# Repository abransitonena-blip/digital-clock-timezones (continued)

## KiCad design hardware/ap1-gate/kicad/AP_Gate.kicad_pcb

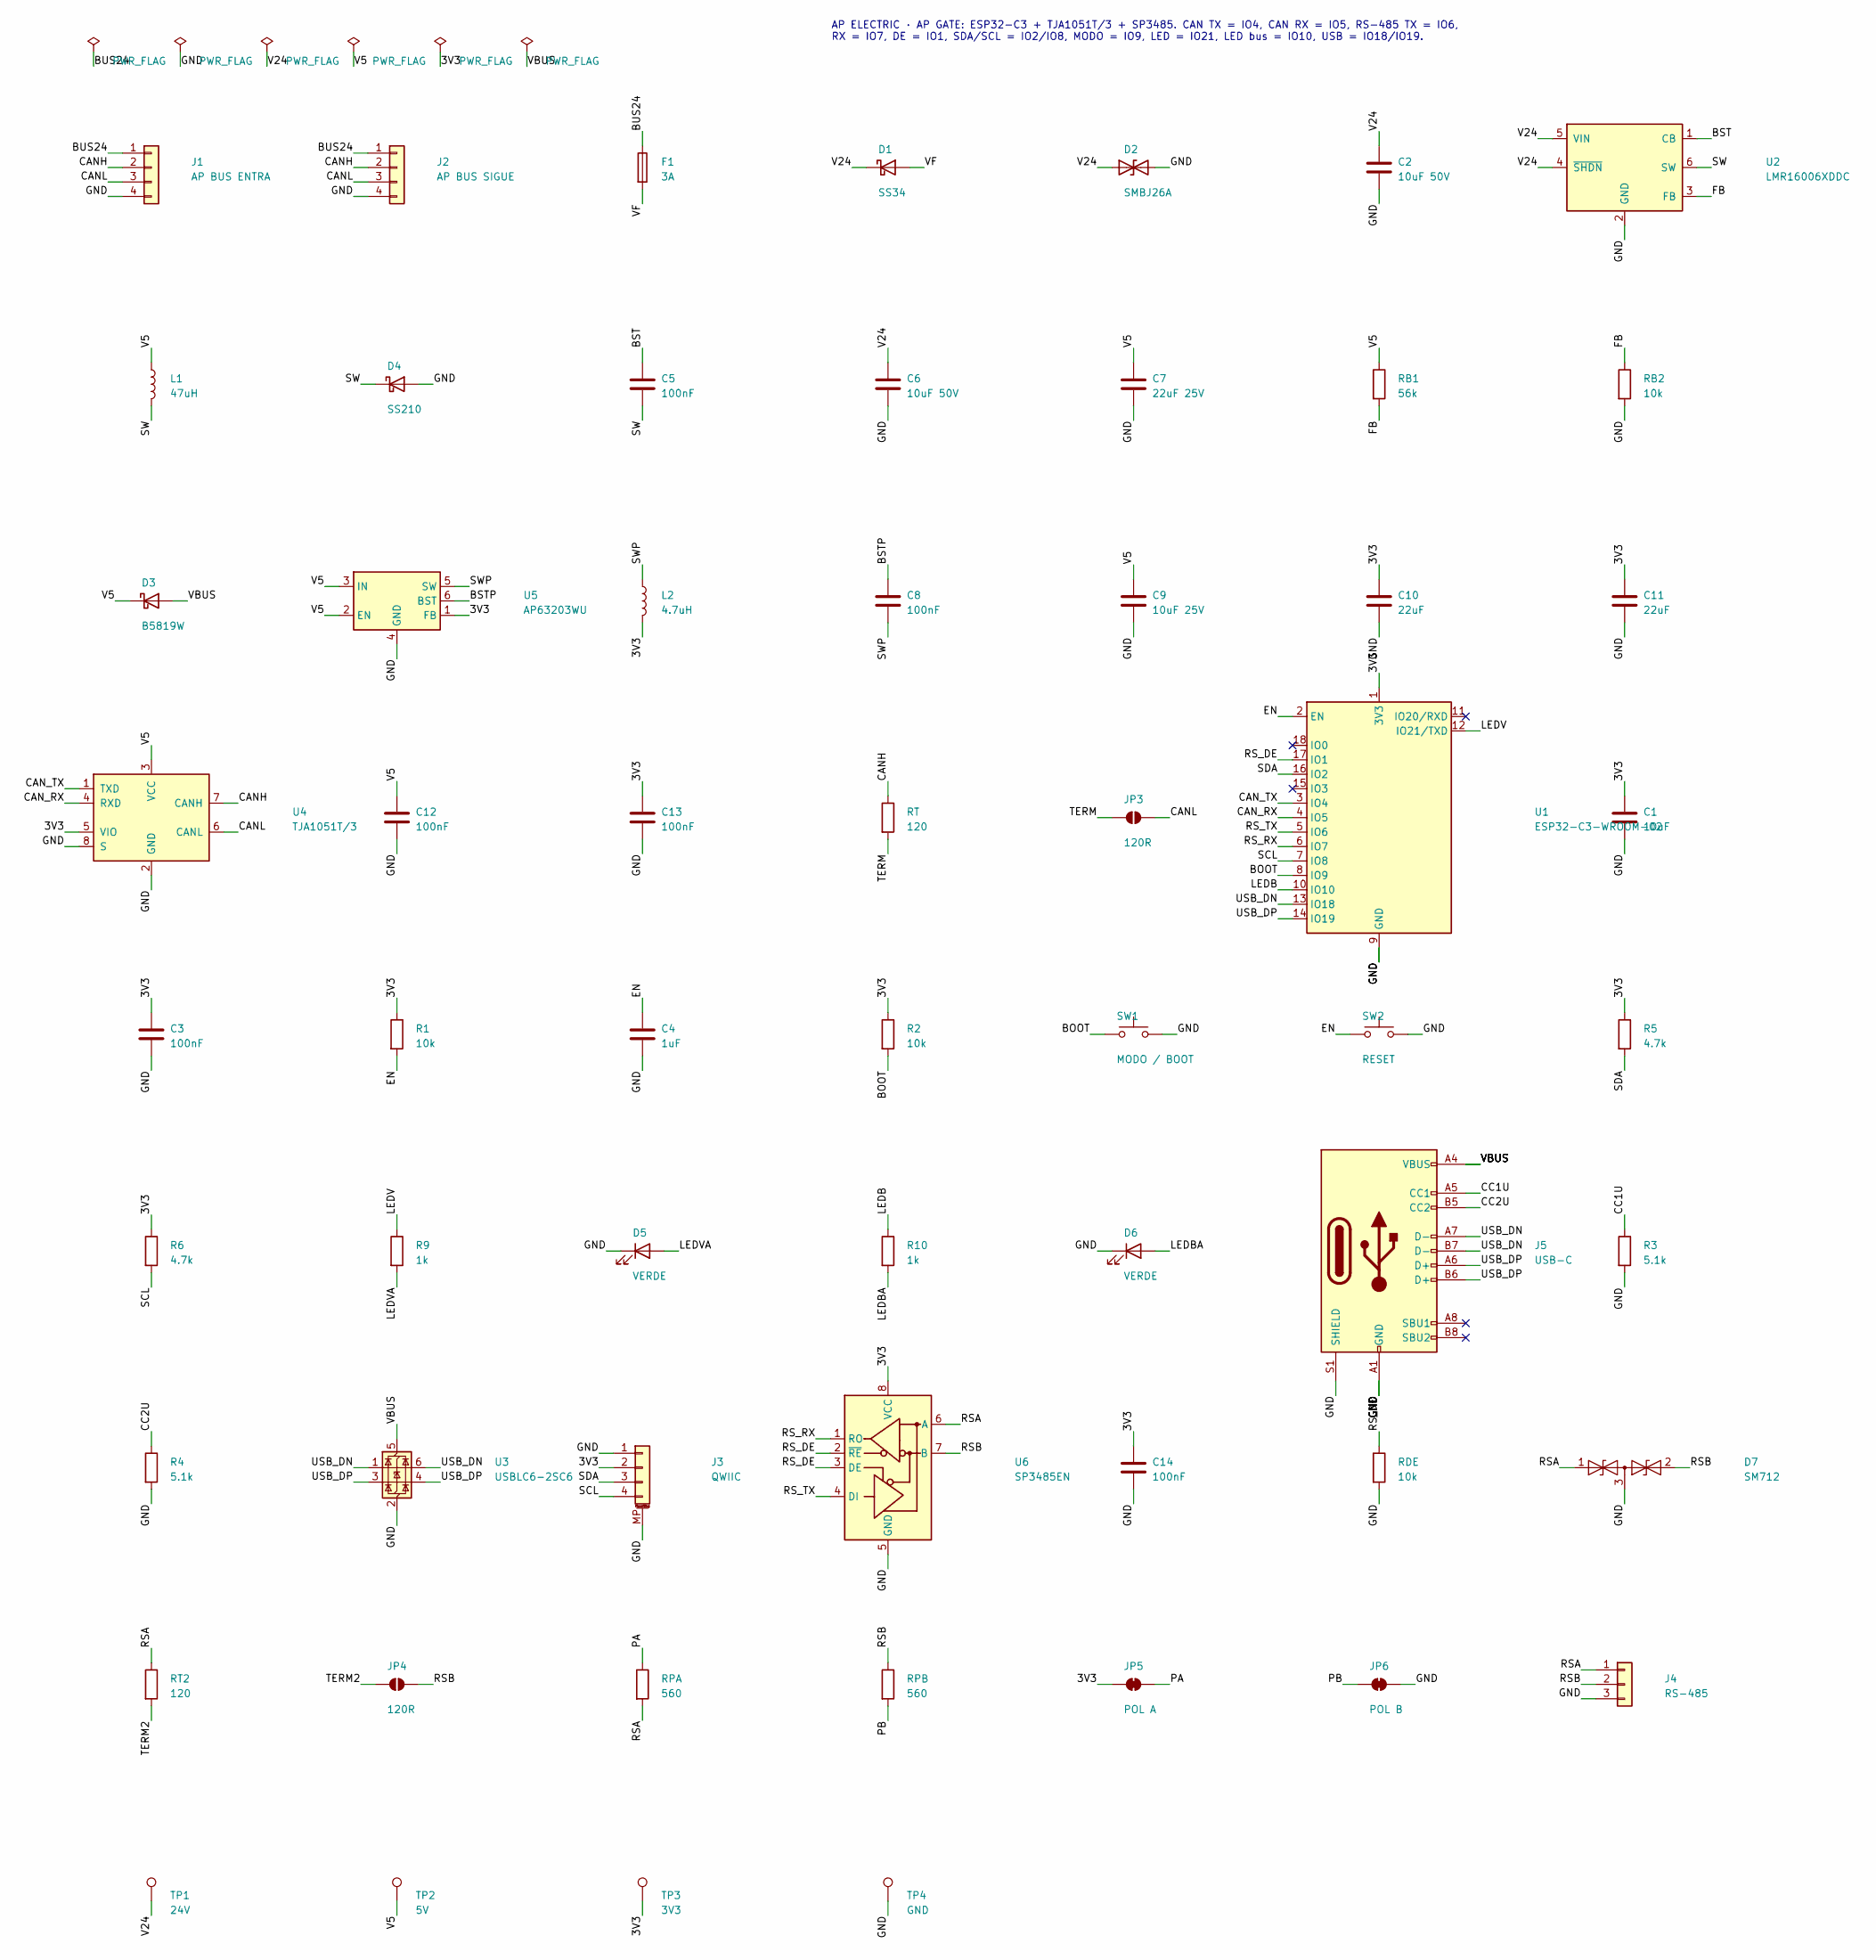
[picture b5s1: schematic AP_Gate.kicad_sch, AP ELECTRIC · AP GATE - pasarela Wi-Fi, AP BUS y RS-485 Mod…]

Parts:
C1: 10uF; C_0805_2012Metric
C2, C6: 10uF 50V; C_1206_3216Metric
C3, C5, C8, C12, C13, C14: 100nF; C_0603_1608Metric
C4: 1uF; C_0603_1608Metric
C7: 22uF 25V; C_1206_3216Metric
C9: 10uF 25V; C_1206_3216Metric
C10, C11: 22uF; C_0805_2012Metric
D1: SS34; D_SMA
D2: SMBJ26A; D_SMB
D3: B5819W; D_SOD-123
D4: SS210; D_SMA
D5, D6: VERDE; LED_0603_1608Metric
D7: SM712; SOT-23
F1: 3A; Fuse_1206_3216Metric
J1: AP BUS ENTRA; JST_XH_B4B-XH-A_1x04_P2.50mm_Vertical
J2: AP BUS SIGUE; JST_XH_B4B-XH-A_1x04_P2.50mm_Vertical
J3: QWIIC; JST_SH_SM04B-SRSS-TB_1x04-1MP_P1.00mm_Horizontal
J4: RS-485; JST_XH_B3B-XH-A_1x03_P2.50mm_Vertical
J5: USB-C; USB_C_Receptacle_HRO_TYPE-C-31-M-12
JP3, JP4: 120R; SolderJumper-2_P1.3mm_Open_RoundedPad1.0x1.5mm
JP5: POL A; SolderJumper-2_P1.3mm_Bridged_RoundedPad1.0x1.5mm
JP6: POL B; SolderJumper-2_P1.3mm_Bridged_RoundedPad1.0x1.5mm
L1: 47uH; L_Changjiang_FNR4030S
L2: 4.7uH; L_Changjiang_FNR4030S
R1, R2: 10k; R_0603_1608Metric
R3, R4: 5.1k; R_0603_1608Metric
R5, R6: 4.7k; R_0603_1608Metric
R9, R10: 1k; R_0603_1608Metric
RB1: 56k; R_0603_1608Metric
RB2: 10k; R_0603_1608Metric
RDE: 10k; R_0603_1608Metric
RPA: 560; R_0603_1608Metric
RPB: 560; R_0603_1608Metric
RT, RT2: 120; R_1206_3216Metric
SW1: MODO / BOOT; SW_Push_1P1T_XKB_TS-1187A
SW2: RESET; SW_Push_1P1T_XKB_TS-1187A
TP1: 24V; TestPoint_Pad_D1.5mm
TP2: 5V; TestPoint_Pad_D1.5mm
TP3: 3V3; TestPoint_Pad_D1.5mm
TP4: GND; TestPoint_Pad_D1.5mm
U1: ESP32-C3-WROOM-02; ESP32-C3-WROOM-02_JLC
U2: LMR16006XDDC; SOT-23-6
U3: USBLC6-2SC6; SOT-23-6
U4: TJA1051T/3; SOIC-8_3.9x4.9mm_P1.27mm
U5: AP63203WU; TSOT-23-6
U6: SP3485EN; SOIC-8_3.9x4.9mm_P1.27mm

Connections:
/3V3: C1.1, C3.1, C10.1, C11.1, C13.1, C14.1, J3.2, JP5.1 (A), L2.2, R1.1, R2.1, R5.1, R6.1, TP3.1, U1.1 (3V3), U4.5 (VIO), U5.1 (FB), U6.8 (VCC)
/BOOT: R2.2, SW1.1, U1.8 (IO9)
/BST: C5.1, U2.1 (CB)
/BSTP: C8.1, U5.6 (BST)
/BUS24: F1.1, J1.1, J2.1
/CANH: J1.2, J2.2, RT.1, U4.7 (CANH)
/CANL: J1.3, J2.3, JP3.2 (B), U4.6 (CANL)
/CAN_RX: U1.4 (IO5), U4.4 (RXD)
/CAN_TX: U1.3 (IO4), U4.1 (TXD)
/CC1U: J5.A5 (CC1), R3.1
/CC2U: J5.B5 (CC2), R4.1
/EN: C4.1, R1.2, SW2.1, U1.2 (EN)
/FB: RB1.2, RB2.1, U2.3 (FB)
/GND: C1.2, C2.2, C3.2, C4.2, C6.2, C7.2, C9.2, C10.2, C11.2, C12.2, C13.2, C14.2, D2.2 (A2), D4.2 (A), D5.1 (K), D6.1 (K), D7.3 (common), J1.4, J2.4, J3.1, J3.MP (MountPin), J4.3, J5.A1 (GND), J5.A12 (GND), J5.B1 (GND), J5.B12 (GND), J5.S1 (SHIELD), JP6.2 (B), R3.2, R4.2, RB2.2, RDE.2, SW1.2, SW2.2, TP4.1, U1.9 (GND), U1.19 (GND), U2.2 (GND), U3.2 (GND), U4.2 (GND), U4.8 (S), U5.4 (GND), U6.5 (GND)
/LEDB: R10.1, U1.10 (IO10)
/LEDBA: D6.2 (A), R10.2
/LEDV: R9.1, U1.12 (IO21/TXD)
/LEDVA: D5.2 (A), R9.2
/PA: JP5.2 (B), RPA.1
/PB: JP6.1 (A), RPB.2
/RSA: D7.1 (A1), J4.1, RPA.2, RT2.1, U6.6 (A)
/RSB: D7.2 (A2), J4.2, JP4.2 (B), RPB.1, U6.7 (B)
/RS_DE: RDE.1, U1.17 (IO1), U6.2 (~RE), U6.3 (DE)
/RS_RX: U1.6 (IO7), U6.1 (RO)
/RS_TX: U1.5 (IO6), U6.4 (DI)
/SCL: J3.4, R6.2, U1.7 (IO8)
/SDA: J3.3, R5.2, U1.16 (IO2)
/SW: C5.2, D4.1 (K), L1.2, U2.6 (SW)
/SWP: C8.2, L2.1, U5.5 (SW)
/TERM: JP3.1 (A), RT.2
/TERM2: JP4.1 (A), RT2.2
/USB_DN: J5.A7 (D-), J5.B7 (D-), U1.13 (IO18), U3.1 (I/O1), U3.6 (I/O1)
/USB_DP: J5.A6 (D+), J5.B6 (D+), U1.14 (IO19), U3.3 (I/O2), U3.4 (I/O2)
/V5: C7.1, C9.1, C12.1, D3.1 (K), L1.1, RB1.1, TP2.1, U4.3 (VCC), U5.2 (EN), U5.3 (IN)
/V24: C2.1, C6.1, D1.1 (K), D2.1 (A1), TP1.1, U2.4 (~SHDN), U2.5 (VIN)
/VBUS: D3.2 (A), J5.A4 (VBUS), J5.A9 (VBUS), J5.B4 (VBUS), J5.B9 (VBUS), U3.5 (VBUS)
/VF: D1.2 (A), F1.2

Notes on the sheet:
AP ELECTRIC · AP GATE: ESP32-C3 + TJA1051T/3 + SP3485. CAN TX = IO4, CAN RX = IO5, RS-485 TX = IO6, RX = IO7, DE = IO1, SDA/SCL = IO2/IO8, MODO = IO9, LED = IO21, LED bus = IO10, USB = IO18/IO19.

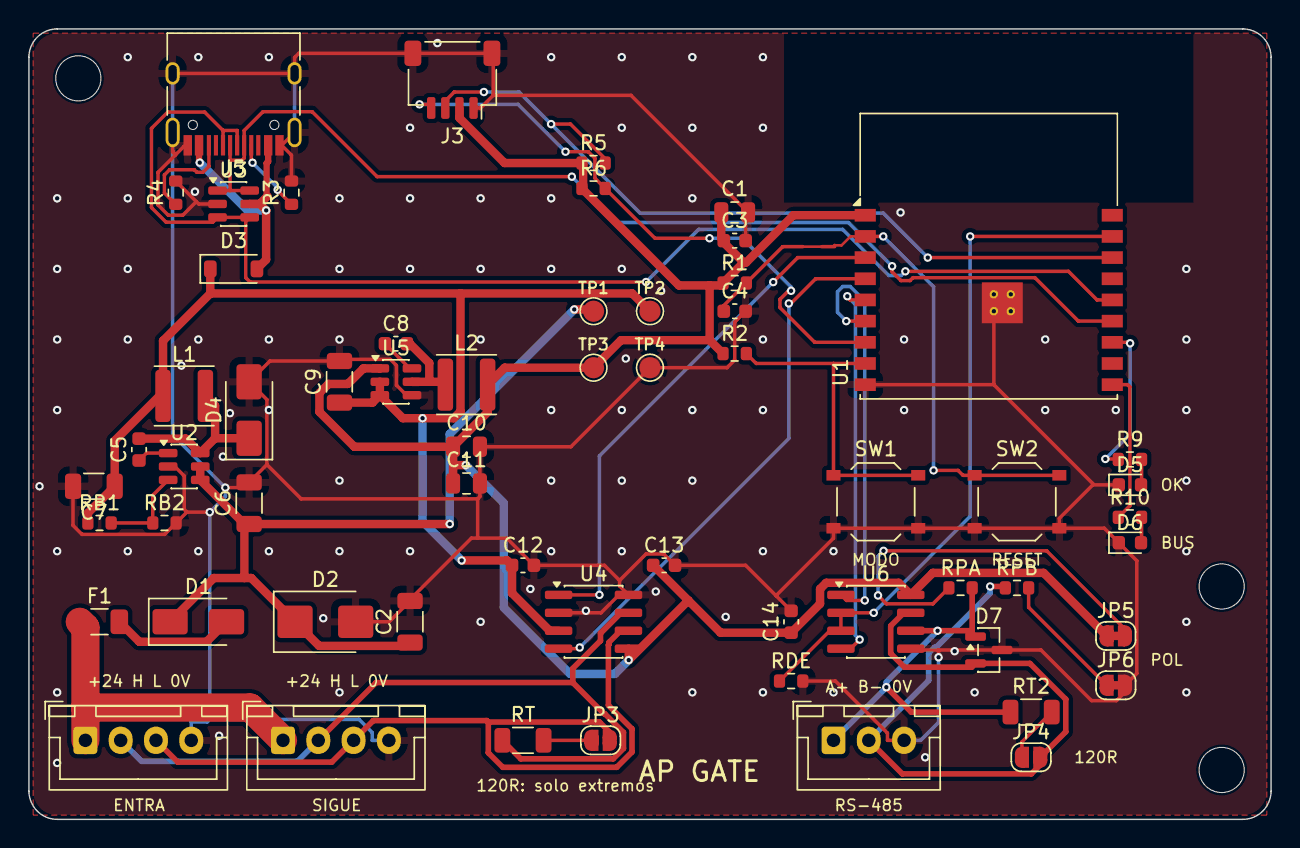
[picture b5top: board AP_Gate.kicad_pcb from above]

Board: 2 copper layers, 88.0 x 56.0 mm, 63 parts (0 on the bottom side), 37 nets.

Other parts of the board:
H1, H2, H3: MountingHole_3.2mm_M3

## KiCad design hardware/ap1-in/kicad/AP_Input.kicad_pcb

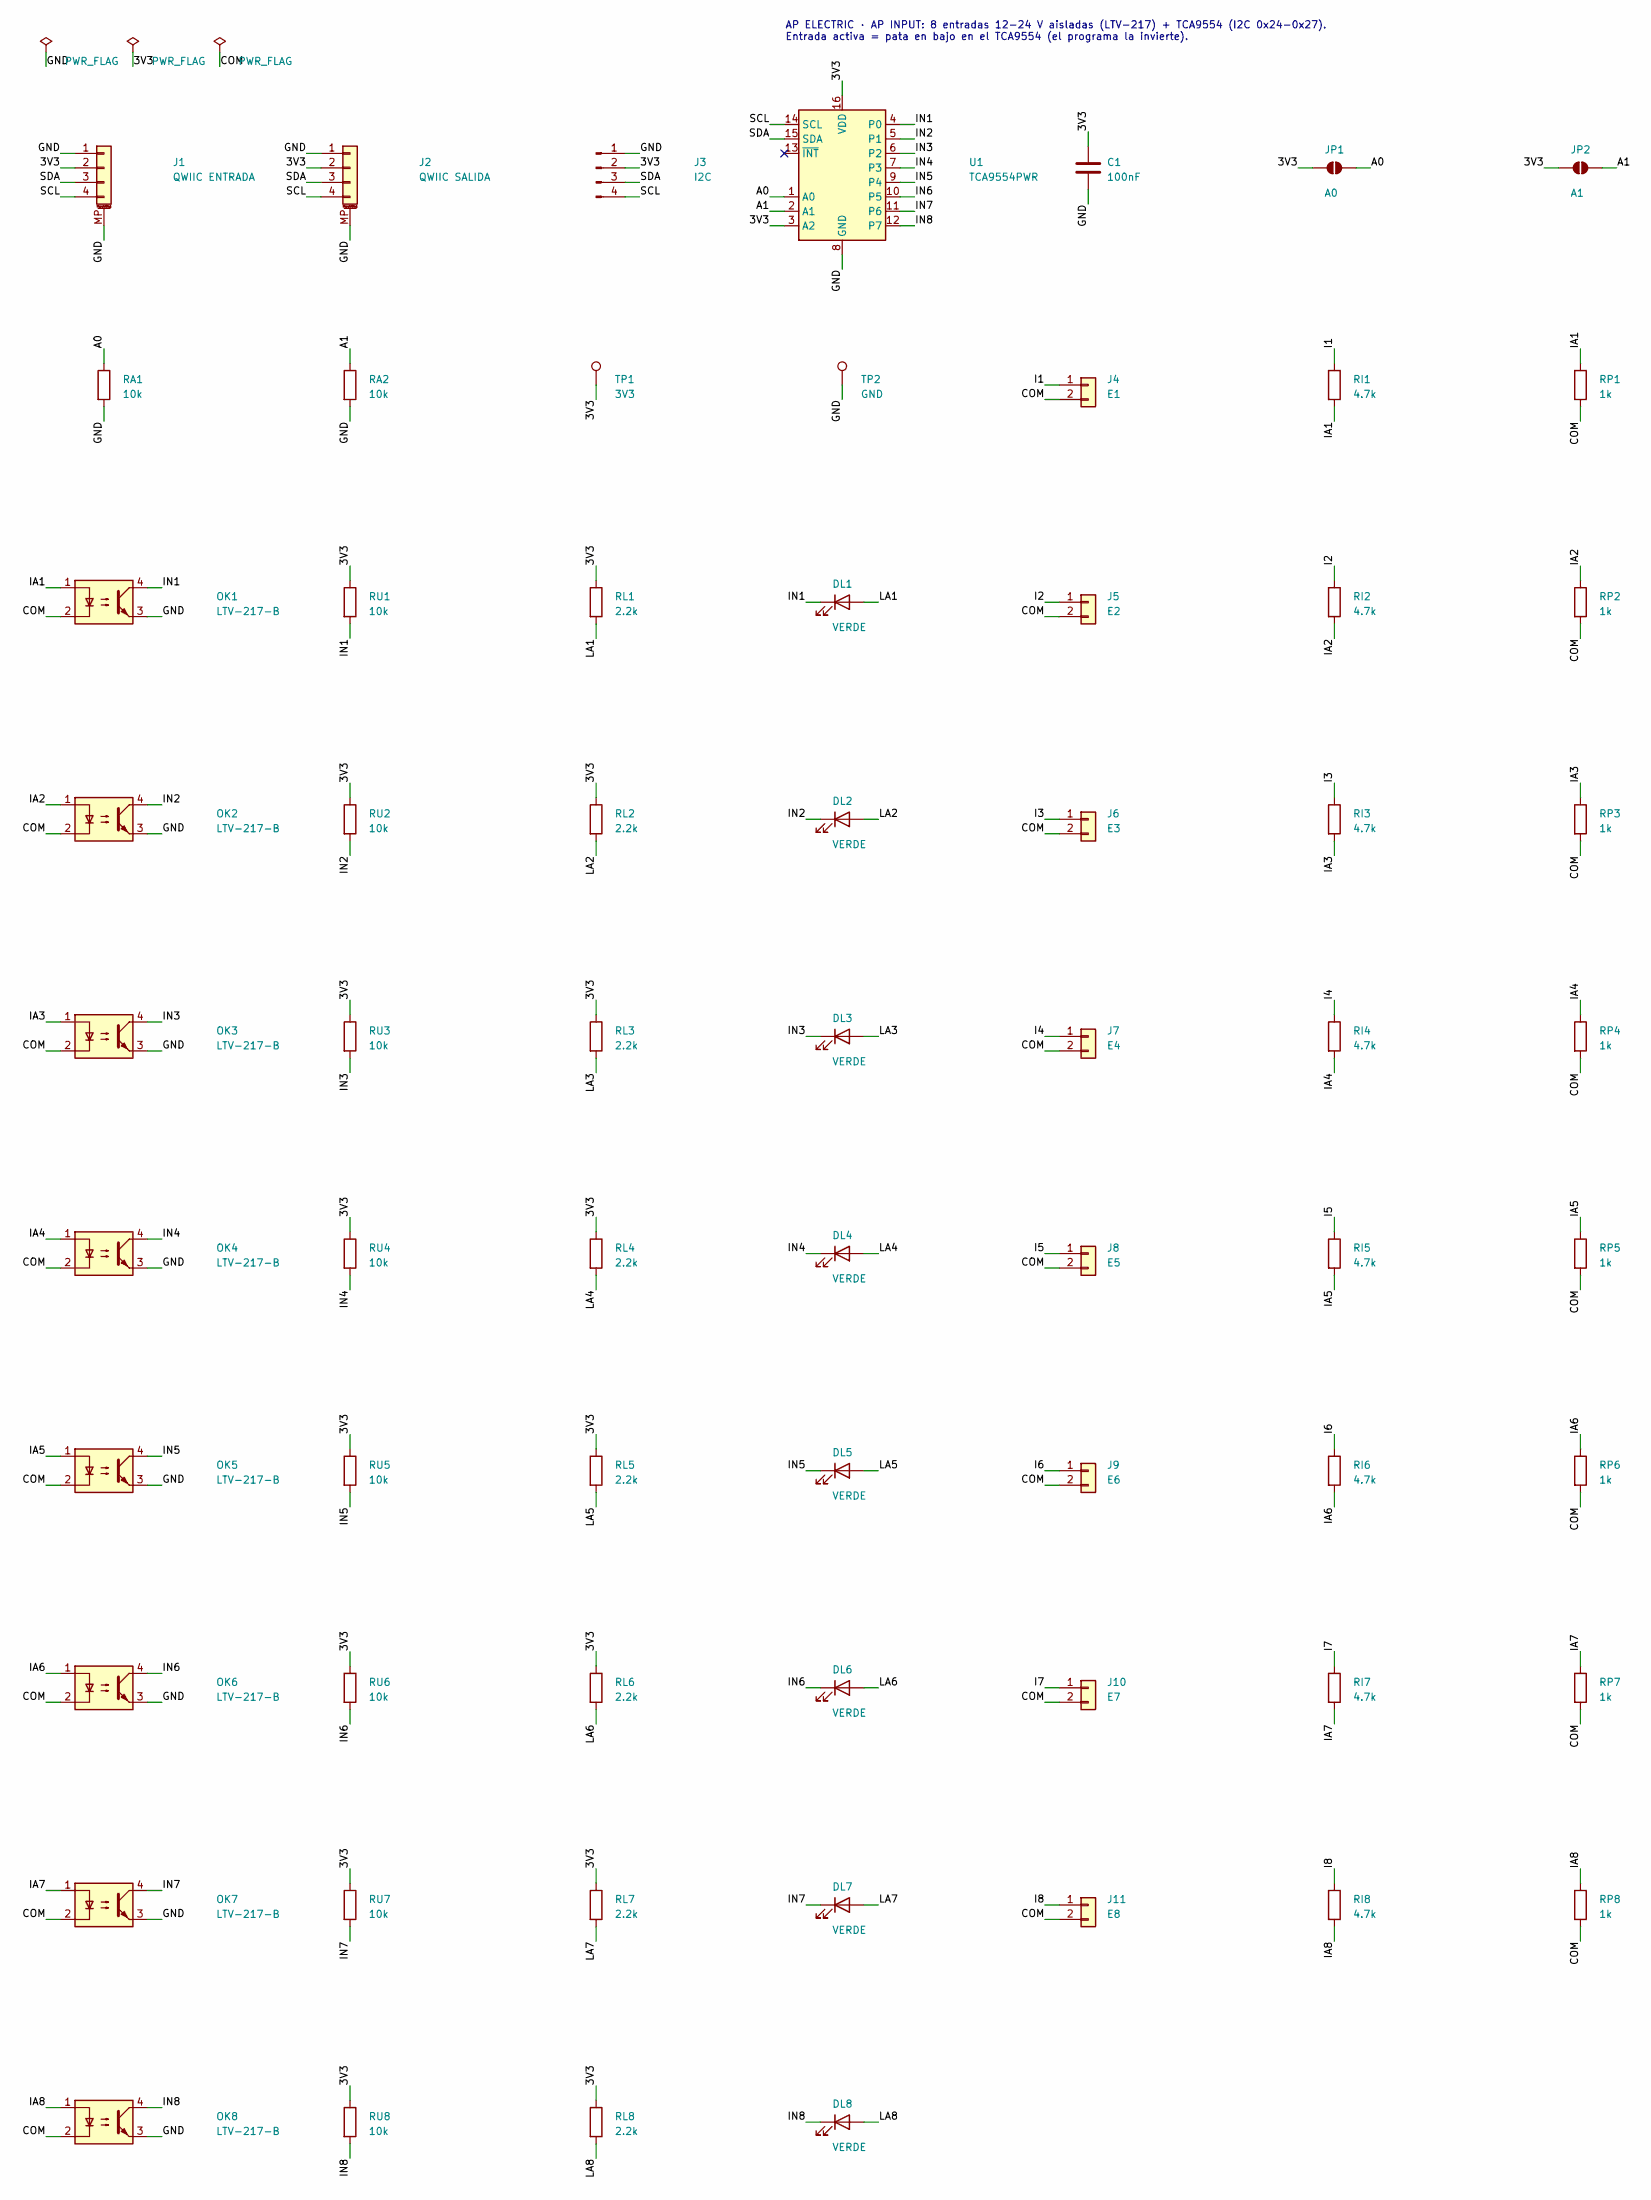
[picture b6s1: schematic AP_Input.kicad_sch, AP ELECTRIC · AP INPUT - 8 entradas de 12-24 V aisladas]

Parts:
C1: 100nF; C_0603_1608Metric
DL1, DL2, DL3, DL4, DL5, DL6, DL7, DL8: VERDE; LED_0603_1608Metric
J1: QWIIC ENTRADA; JST_SH_SM04B-SRSS-TB_1x04-1MP_P1.00mm_Horizontal
J2: QWIIC SALIDA; JST_SH_SM04B-SRSS-TB_1x04-1MP_P1.00mm_Horizontal
J3: I2C; PinHeader_1x04_P2.54mm_Vertical
J4: E1; JST_XH_B2B-XH-A_1x02_P2.50mm_Vertical
J5: E2; JST_XH_B2B-XH-A_1x02_P2.50mm_Vertical
J6: E3; JST_XH_B2B-XH-A_1x02_P2.50mm_Vertical
J7: E4; JST_XH_B2B-XH-A_1x02_P2.50mm_Vertical
J8: E5; JST_XH_B2B-XH-A_1x02_P2.50mm_Vertical
J9: E6; JST_XH_B2B-XH-A_1x02_P2.50mm_Vertical
J10: E7; JST_XH_B2B-XH-A_1x02_P2.50mm_Vertical
J11: E8; JST_XH_B2B-XH-A_1x02_P2.50mm_Vertical
JP1: A0; SolderJumper-2_P1.3mm_Open_RoundedPad1.0x1.5mm
JP2: A1; SolderJumper-2_P1.3mm_Open_RoundedPad1.0x1.5mm
OK1, OK2, OK3, OK4, OK5, OK6, OK7, OK8: LTV-217-B; SOP-4_4.4x2.6mm_P1.27mm
RA1, RA2: 10k; R_0603_1608Metric
RI1, RI2, RI3, RI4, RI5, RI6, RI7, RI8: 4.7k; R_1206_3216Metric
RL1, RL2, RL3, RL4, RL5, RL6, RL7, RL8: 2.2k; R_0603_1608Metric
RP1, RP2, RP3, RP4, RP5, RP6, RP7, RP8: 1k; R_0603_1608Metric
RU1, RU2, RU3, RU4, RU5, RU6, RU7, RU8: 10k; R_0603_1608Metric
TP1: 3V3; TestPoint_Pad_D1.5mm
TP2: GND; TestPoint_Pad_D1.5mm
U1: TCA9554PWR; TSSOP-16_4.4x5mm_P0.65mm

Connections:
/3V3: C1.1, J1.2, J2.2, J3.2, JP1.1 (A), JP2.1 (A), RL1.1, RL2.1, RL3.1, RL4.1, RL5.1, RL6.1, RL7.1, RL8.1, RU1.1, RU2.1, RU3.1, RU4.1, RU5.1, RU6.1, RU7.1, RU8.1, TP1.1, U1.3 (A2), U1.16 (VDD)
/A0: JP1.2 (B), RA1.1, U1.1 (A0)
/A1: JP2.2 (B), RA2.1, U1.2 (A1)
/COM: J4.2, J5.2, J6.2, J7.2, J8.2, J9.2, J10.2, J11.2, OK1.2, OK2.2, OK3.2, OK4.2, OK5.2, OK6.2, OK7.2, OK8.2, RP1.2, RP2.2, RP3.2, RP4.2, RP5.2, RP6.2, RP7.2, RP8.2
/GND: C1.2, J1.1, J1.MP (MountPin), J2.1, J2.MP (MountPin), J3.1, OK1.3, OK2.3, OK3.3, OK4.3, OK5.3, OK6.3, OK7.3, OK8.3, RA1.2, RA2.2, TP2.1, U1.8 (GND)
/I1: J4.1, RI1.1
/I2: J5.1, RI2.1
/I3: J6.1, RI3.1
/I4: J7.1, RI4.1
/I5: J8.1, RI5.1
/I6: J9.1, RI6.1
/I7: J10.1, RI7.1
/I8: J11.1, RI8.1
/IA1: OK1.1, RI1.2, RP1.1
/IA2: OK2.1, RI2.2, RP2.1
/IA3: OK3.1, RI3.2, RP3.1
/IA4: OK4.1, RI4.2, RP4.1
/IA5: OK5.1, RI5.2, RP5.1
/IA6: OK6.1, RI6.2, RP6.1
/IA7: OK7.1, RI7.2, RP7.1
/IA8: OK8.1, RI8.2, RP8.1
/IN1: DL1.1 (K), OK1.4, RU1.2, U1.4 (P0)
/IN2: DL2.1 (K), OK2.4, RU2.2, U1.5 (P1)
/IN3: DL3.1 (K), OK3.4, RU3.2, U1.6 (P2)
/IN4: DL4.1 (K), OK4.4, RU4.2, U1.7 (P3)
/IN5: DL5.1 (K), OK5.4, RU5.2, U1.9 (P4)
/IN6: DL6.1 (K), OK6.4, RU6.2, U1.10 (P5)
/IN7: DL7.1 (K), OK7.4, RU7.2, U1.11 (P6)
/IN8: DL8.1 (K), OK8.4, RU8.2, U1.12 (P7)
/LA1: DL1.2 (A), RL1.2
/LA2: DL2.2 (A), RL2.2
/LA3: DL3.2 (A), RL3.2
/LA4: DL4.2 (A), RL4.2
/LA5: DL5.2 (A), RL5.2
/LA6: DL6.2 (A), RL6.2
/LA7: DL7.2 (A), RL7.2
/LA8: DL8.2 (A), RL8.2
/SCL: J1.4, J2.4, J3.4, U1.14 (SCL)
/SDA: J1.3, J2.3, J3.3, U1.15 (SDA)

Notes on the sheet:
AP ELECTRIC · AP INPUT: 8 entradas 12-24 V aisladas (LTV-217) + TCA9554 (I2C 0x24-0x27). Entrada activa = pata en bajo en el TCA9554 (el programa la invierte).

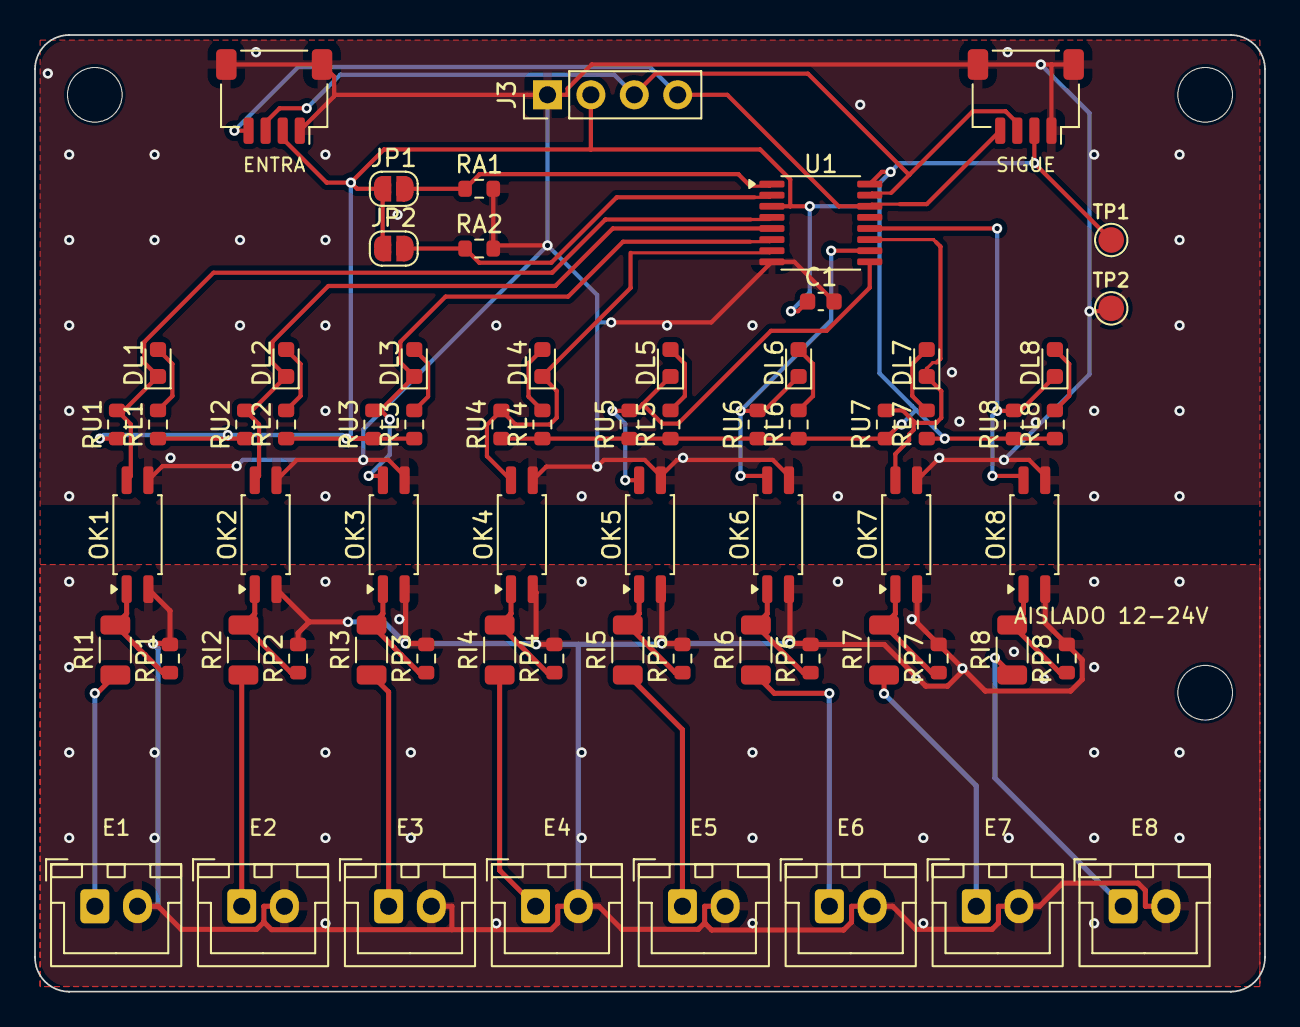
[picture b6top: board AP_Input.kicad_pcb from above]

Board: 2 copper layers, 72.0 x 56.0 mm, 70 parts (0 on the bottom side), 39 nets.

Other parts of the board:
H1, H2, H3: MountingHole_3.2mm_M3

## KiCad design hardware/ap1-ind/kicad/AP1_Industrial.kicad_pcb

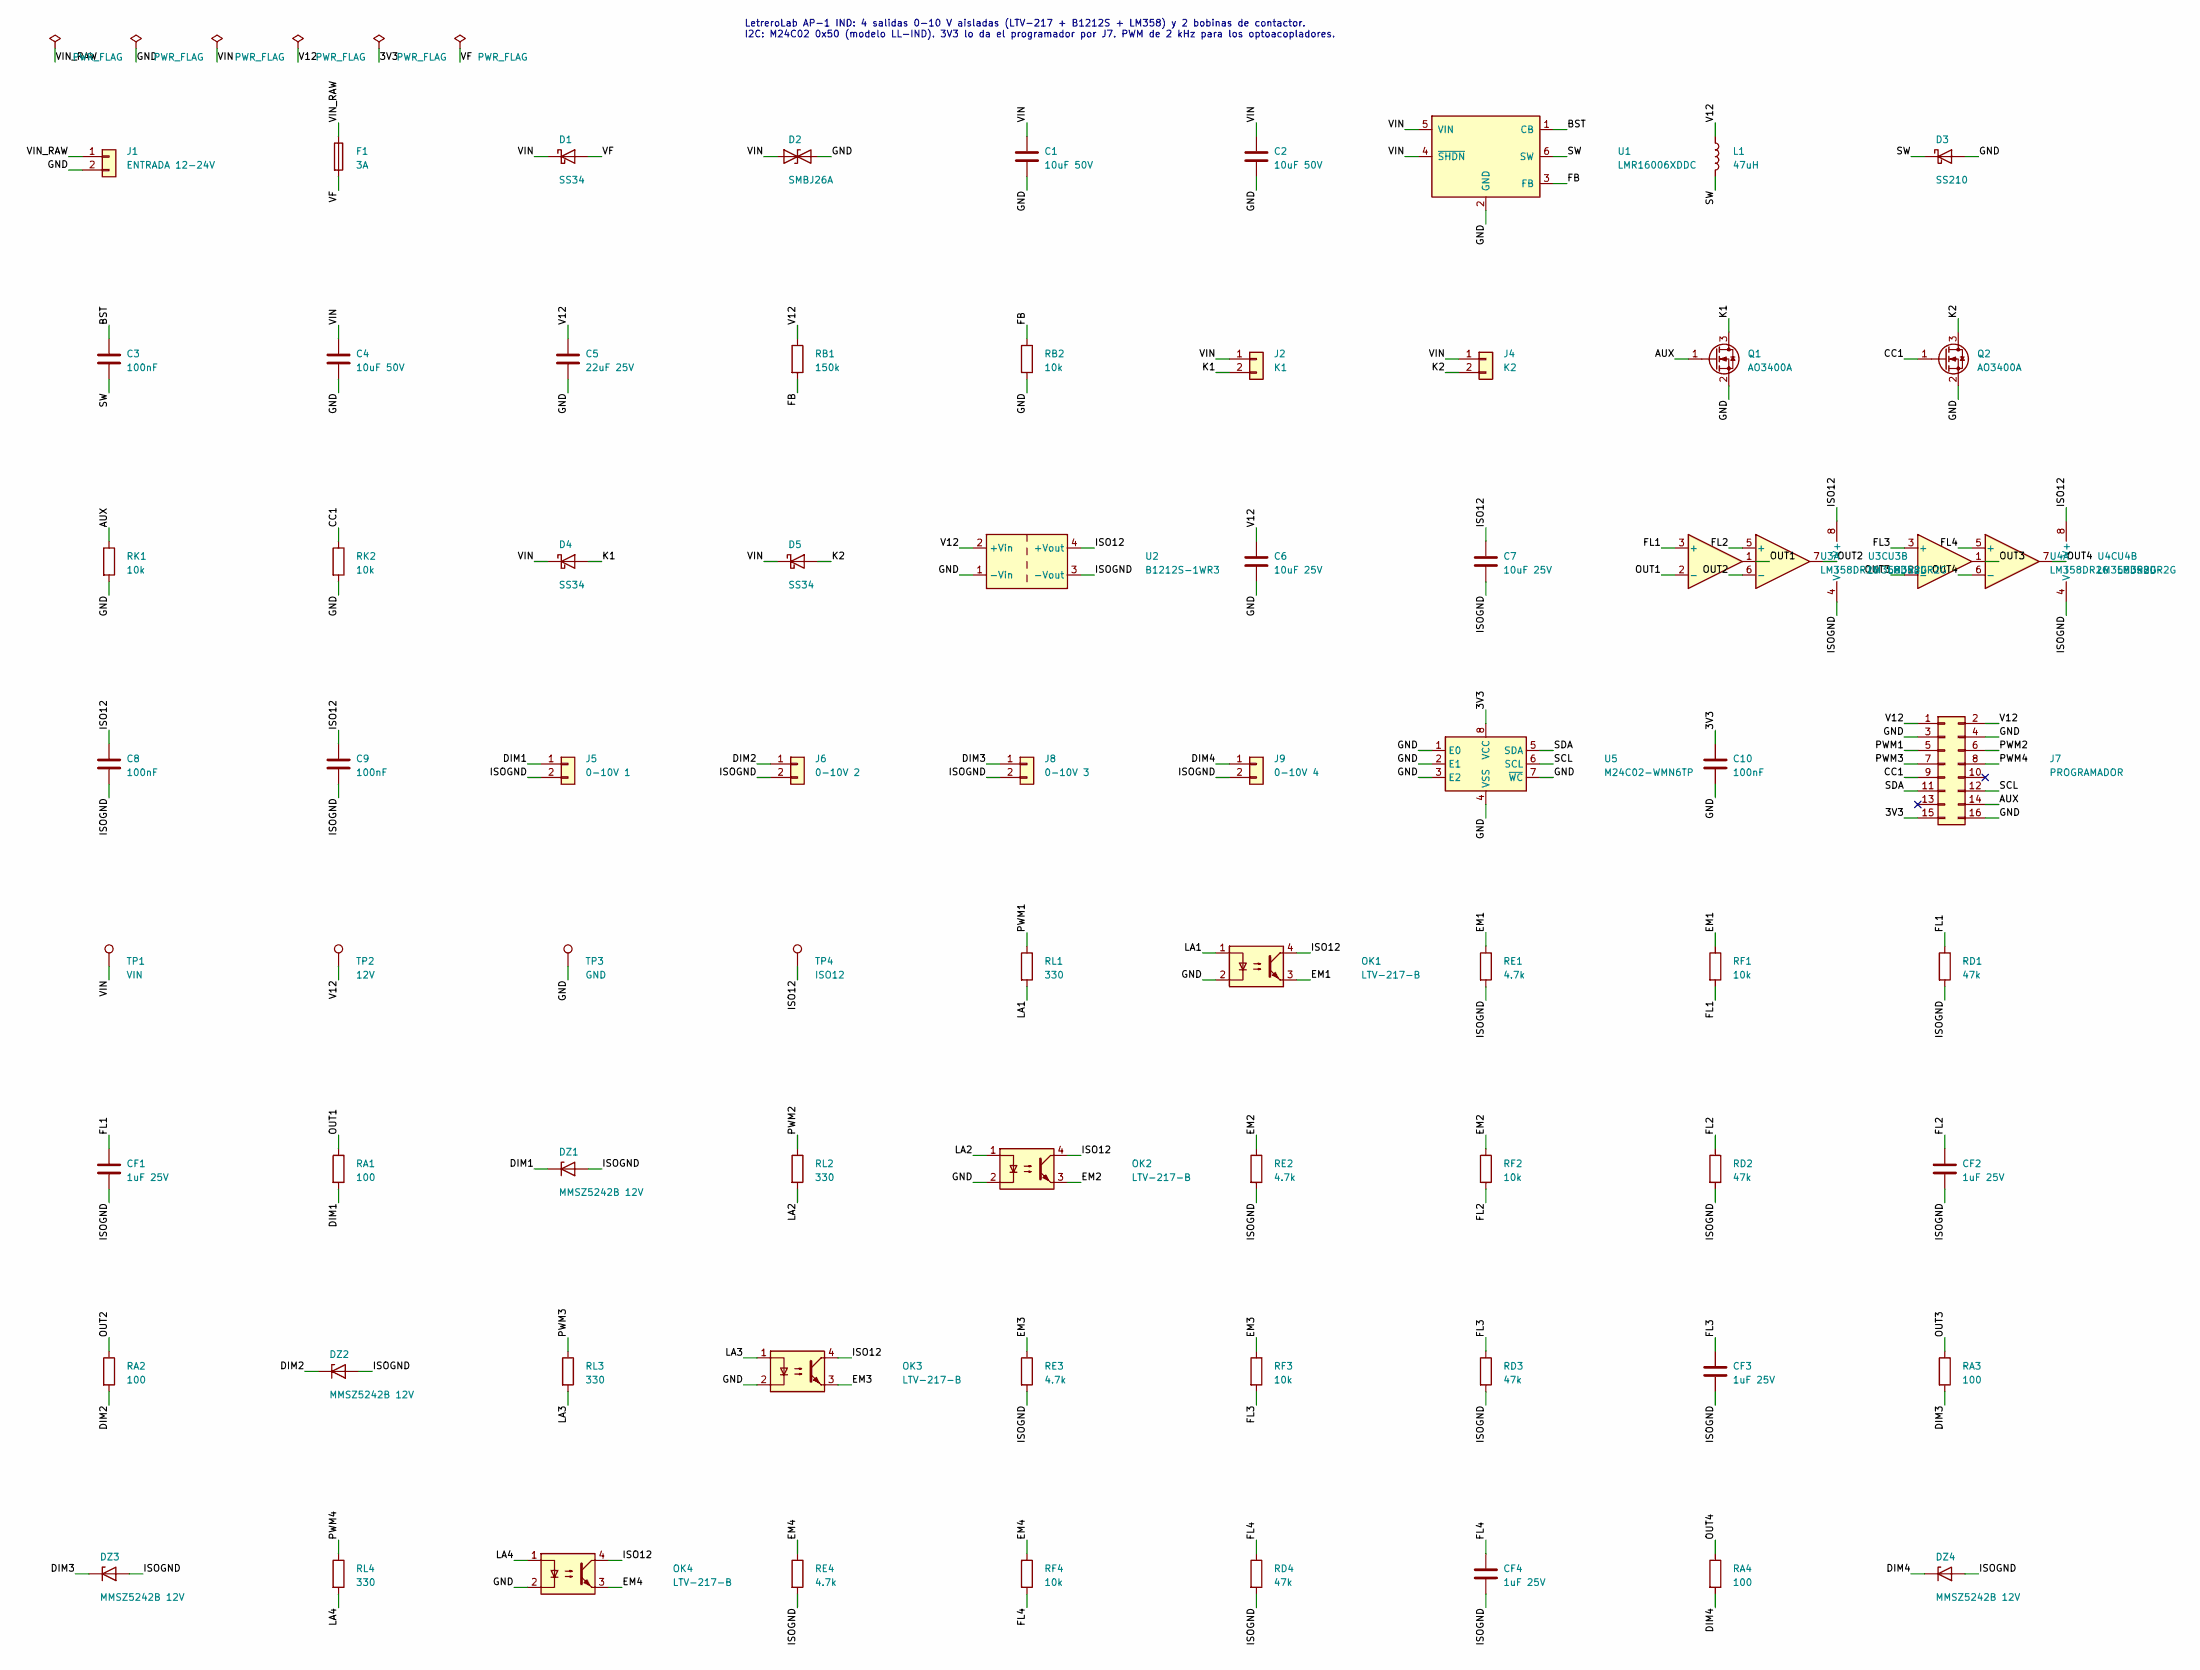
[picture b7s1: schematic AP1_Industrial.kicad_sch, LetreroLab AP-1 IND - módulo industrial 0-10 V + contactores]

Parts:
C1, C2, C4: 10uF 50V; C_1206_3216Metric
C3, C8, C9, C10: 100nF; C_0603_1608Metric
C5: 22uF 25V; C_1206_3216Metric
C6, C7: 10uF 25V; C_1206_3216Metric
CF1, CF2, CF3, CF4: 1uF 25V; C_0603_1608Metric
D1, D4, D5: SS34; D_SMA
D2: SMBJ26A; D_SMB
D3: SS210; D_SMA
DZ1, DZ2, DZ3, DZ4: MMSZ5242B 12V; D_SOD-123
F1: 3A; Fuse_1206_3216Metric
J1: ENTRADA 12-24V; JST_VH_B2P-VH_1x02_P3.96mm_Vertical
J2: K1; JST_XH_B2B-XH-A_1x02_P2.50mm_Vertical
J4: K2; JST_XH_B2B-XH-A_1x02_P2.50mm_Vertical
J5: 0-10V 1; JST_XH_B2B-XH-A_1x02_P2.50mm_Vertical
J6: 0-10V 2; JST_XH_B2B-XH-A_1x02_P2.50mm_Vertical
J7: PROGRAMADOR; PinSocket_2x08_P2.54mm_Vertical
J8: 0-10V 3; JST_XH_B2B-XH-A_1x02_P2.50mm_Vertical
J9: 0-10V 4; JST_XH_B2B-XH-A_1x02_P2.50mm_Vertical
L1: 47uH; L_Changjiang_FNR4030S
OK1, OK2, OK3, OK4: LTV-217-B; SOP-4_4.4x2.6mm_P1.27mm
Q1, Q2: AO3400A; SOT-23
RA1, RA2, RA3, RA4: 100; R_0603_1608Metric
RB1: 150k; R_0603_1608Metric
RB2: 10k; R_0603_1608Metric
RD1, RD2, RD3, RD4: 47k; R_0603_1608Metric
RE1, RE2, RE3, RE4: 4.7k; R_0603_1608Metric
RF1, RF2, RF3, RF4: 10k; R_0603_1608Metric
RK1, RK2: 10k; R_0603_1608Metric
RL1, RL2, RL3, RL4: 330; R_0603_1608Metric
TP1: VIN; TestPoint_Pad_D1.5mm
TP2: 12V; TestPoint_Pad_D1.5mm
TP3: GND; TestPoint_Pad_D1.5mm
TP4: ISO12; TestPoint_Pad_D1.5mm
U1: LMR16006XDDC; SOT-23-6
U2: B1212S-1WR3; Converter_DCDC_Murata_MEE1SxxxxSC_THT
U3, U4: LM358DR2G; SOIC-8_3.9x4.9mm_P1.27mm
U5: M24C02-WMN6TP; SOIC-8_3.9x4.9mm_P1.27mm

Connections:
/3V3: C10.1, J7.15, U5.8 (VCC)
/AUX: J7.14, Q1.1 (G), RK1.1
/BST: C3.1, U1.1 (CB)
/CC1: J7.9, Q2.1 (G), RK2.1
/DIM1: DZ1.1 (K), J5.1, RA1.2
/DIM2: DZ2.1 (K), J6.1, RA2.2
/DIM3: DZ3.1 (K), J8.1, RA3.2
/DIM4: DZ4.1 (K), J9.1, RA4.2
/EM1: OK1.3, RE1.1, RF1.1
/EM2: OK2.3, RE2.1, RF2.1
/EM3: OK3.3, RE3.1, RF3.1
/EM4: OK4.3, RE4.1, RF4.1
/FB: RB1.2, RB2.1, U1.3 (FB)
/FL1: CF1.1, RD1.1, RF1.2, U3.3 (+)
/FL2: CF2.1, RD2.1, RF2.2, U3.5 (+)
/FL3: CF3.1, RD3.1, RF3.2, U4.3 (+)
/FL4: CF4.1, RD4.1, RF4.2, U4.5 (+)
/GND: C1.2, C2.2, C4.2, C5.2, C6.2, C10.2, D2.2 (A2), D3.2 (A), J1.2, J7.3, J7.4, J7.16, OK1.2, OK2.2, OK3.2, OK4.2, Q1.2 (S), Q2.2 (S), RB2.2, RK1.2, RK2.2, TP3.1, U1.2 (GND), U2.1 (-Vin), U5.1 (E0), U5.2 (E1), U5.3 (E2), U5.4 (VSS), U5.7 (~WC)
/ISO12: C7.1, C8.1, C9.1, OK1.4, OK2.4, OK3.4, OK4.4, TP4.1, U2.4 (+Vout), U3.8 (V+), U4.8 (V+)
/ISOGND: C7.2, C8.2, C9.2, CF1.2, CF2.2, CF3.2, CF4.2, DZ1.2 (A), DZ2.2 (A), DZ3.2 (A), DZ4.2 (A), J5.2, J6.2, J8.2, J9.2, RD1.2, RD2.2, RD3.2, RD4.2, RE1.2, RE2.2, RE3.2, RE4.2, U2.3 (-Vout), U3.4 (V-), U4.4 (V-)
/K1: D4.2 (A), J2.2, Q1.3 (D)
/K2: D5.2 (A), J4.2, Q2.3 (D)
/LA1: OK1.1, RL1.2
/LA2: OK2.1, RL2.2
/LA3: OK3.1, RL3.2
/LA4: OK4.1, RL4.2
/OUT1: RA1.1, U3.1, U3.2 (-)
/OUT2: RA2.1, U3.6 (-), U3.7
/OUT3: RA3.1, U4.1, U4.2 (-)
/OUT4: RA4.1, U4.6 (-), U4.7
/PWM1: J7.5, RL1.1
/PWM2: J7.6, RL2.1
/PWM3: J7.7, RL3.1
/PWM4: J7.8, RL4.1
/SCL: J7.12, U5.6 (SCL)
/SDA: J7.11, U5.5 (SDA)
/SW: C3.2, D3.1 (K), L1.2, U1.6 (SW)
/V12: C5.1, C6.1, J7.1, J7.2, L1.1, RB1.1, TP2.1, U2.2 (+Vin)
/VF: D1.2 (A), F1.2
/VIN: C1.1, C2.1, C4.1, D1.1 (K), D2.1 (A1), D4.1 (K), D5.1 (K), J2.1, J4.1, TP1.1, U1.4 (~SHDN), U1.5 (VIN)
/VIN_RAW: F1.1, J1.1

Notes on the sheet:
LetreroLab AP-1 IND: 4 salidas 0-10 V aisladas (LTV-217 + B1212S + LM358) y 2 bobinas de contactor. I2C: M24C02 0x50 (modelo LL-IND). 3V3 lo da el programador por J7. PWM de 2 kHz para los optoacopladores.

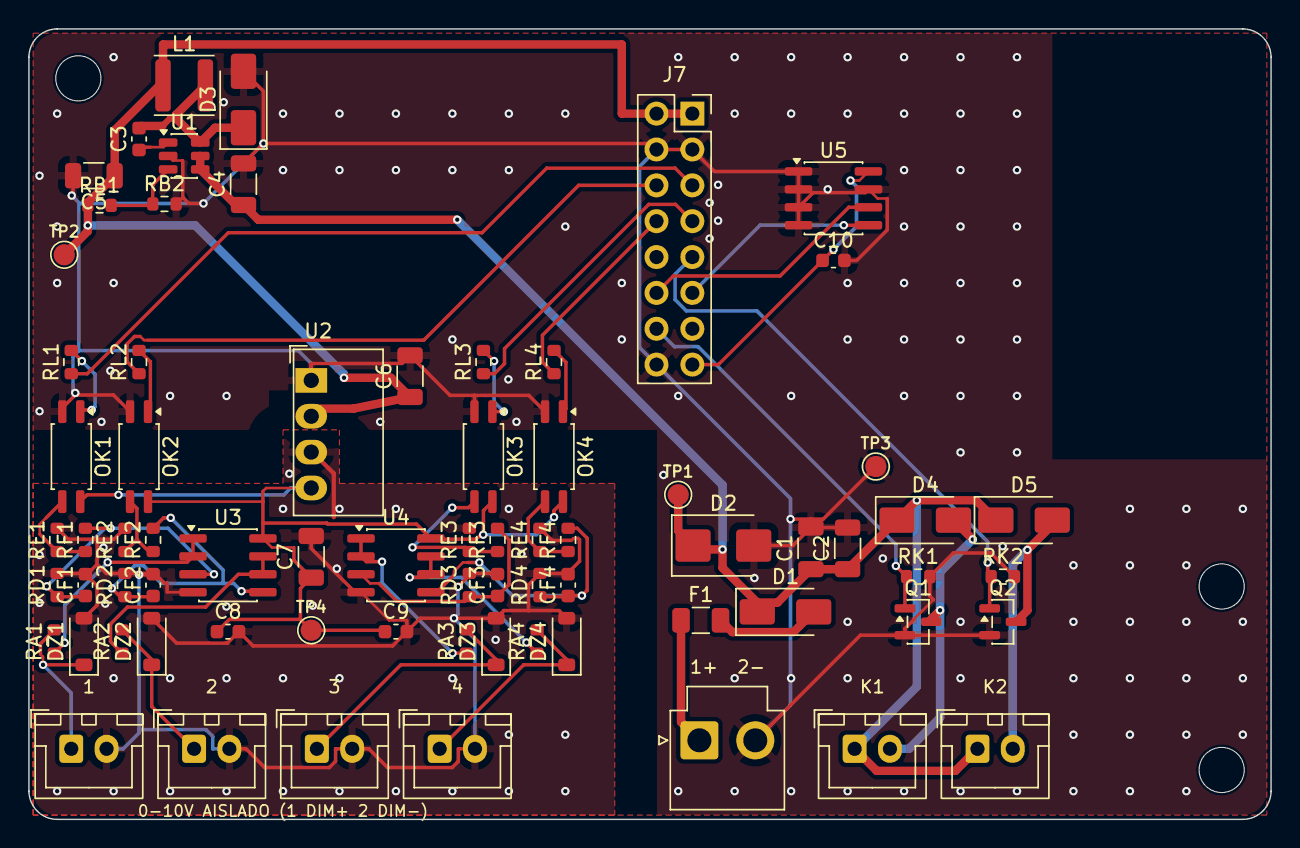
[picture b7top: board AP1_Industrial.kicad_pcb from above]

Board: 2 copper layers, 88.0 x 56.0 mm, 75 parts (0 on the bottom side), 41 nets.

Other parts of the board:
H1, H2, H3: MountingHole_3.2mm_M3
